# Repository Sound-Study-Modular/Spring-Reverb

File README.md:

# Spring-Reverb

The Spring Reverb is a flexible, easy-to-build voltage controlled DIY mono spring reverb module. Traditional guitar reverbs are tuned to the sound of the guitar and the amplifier it is played through. This circuit is different; designed to be relatively clean and high-fi, with a lot of bass response. It can also be abused and driven into (externally patched) feedback.

The circuit, plans and PCB/panel designs are open source and shared under Creative Commons.

- Works with a variety of spring reverb tanks, or with the Accutronics BTDR-2 reverb ‘brick’ designed by Brian Neunaber
- Includes PCB panel designs that can be very cheaply produced.
- Vactrol crossfade between dry and wet
- Tilt EQ on the reverb send to tune the voice of the reverb
- X-Fade input so the module can also be used as a standalone vactrol crossfader
- Attenuverter on the crossfade CV input
- Options for reverb tank connection and placement including front panel sockets.
- Optional (unbuffered) PCB connections for 100% wet and post-EQ dry outputs
- 6hp wide (NB: If using the brick, mounted horizontally, the brick extends 5mm over the PCB to the left of the module, around 25mm back from the front panel, so mount the reverb next to a shallow module)
- Around 60mm deep including a phono plug for the reverb tank coming from the back. Just 35mm deep if you mount the reverb connections on the front panel

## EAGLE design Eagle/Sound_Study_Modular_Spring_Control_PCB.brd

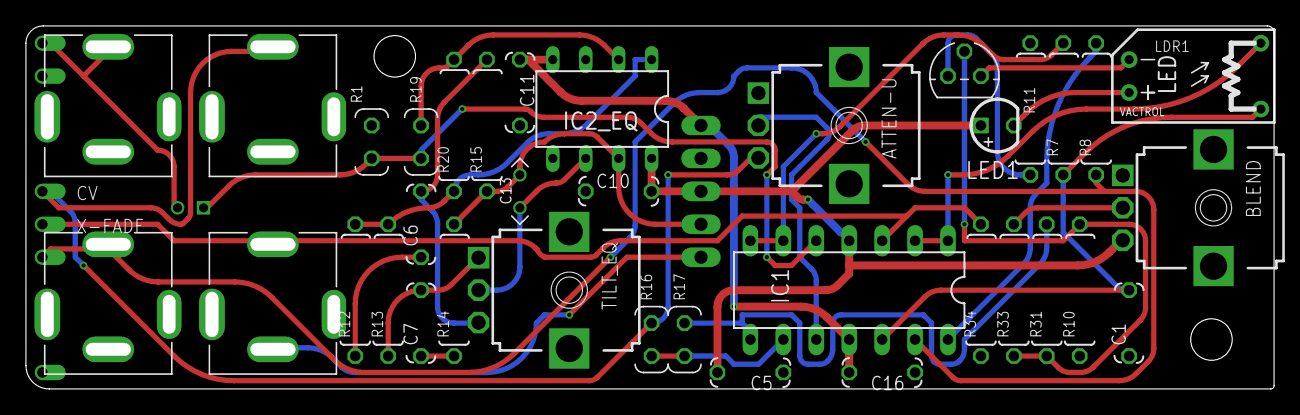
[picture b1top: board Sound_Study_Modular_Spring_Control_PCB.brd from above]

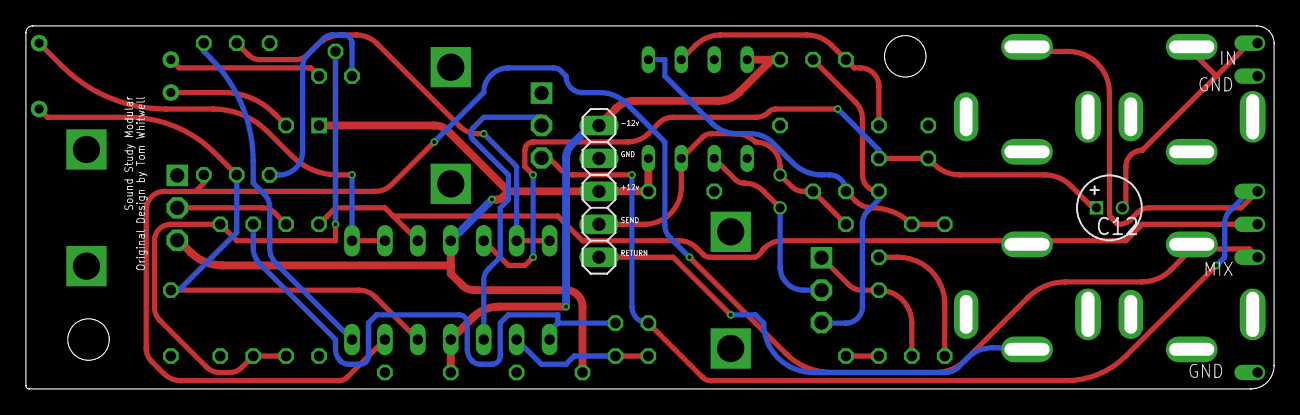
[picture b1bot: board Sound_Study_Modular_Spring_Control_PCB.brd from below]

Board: 4 copper layers, 96.3 x 28.0 mm, 44 parts (2 on the bottom side), 29 nets.

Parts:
ATTEN-U: 50k; EVUF
BLEND: 50k; EVUF
C1: 1nf; C050-024X044
C5, C10, C11, C16: 100n; C050-024X044
C6, C7: 33nf; C050-024X044
C12: 10uf; 050_020
C13: 22pf; 050X030_025
CV: ERTHENVAR
IC1: TL074; DIL14
IC2_EQ: NE5532; DIL08
IN: MONO_JACK_W_SWITCH; ERTHENVAR
JP3: 1X05
LDR1: VTL5C; VACTROL_COMPACT
LED1: 3mm Superbright; LED3MM
OUT: ERTHENVAR
R1: 100k; VERT-RESISTOR
R7: 0207/10
R8: 1k; 0207/10
R10, R31, R33, R34: 100k; 0207/10
R11, R12, R14: 2.2k; 0207/10
R13, R15: 6.8k; 0207/10
R16, R17: 47k; VERT-RESISTOR
R19: 10k; VERT-RESISTOR
R20: 10k; 0207/10
T1: 2N3904; TO92
TILT_EQ: 10k; EVUF
U$3: X-FADE; LONG_PAD_1
U$9, U$16: GND; LONG_PAD_1
U$13: IN; LONG_PAD_1
U$14: CV; LONG_PAD_1
U$17: MIX; LONG_PAD_1
X_FADE: ERTHENVAR

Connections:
+12V: BLEND.3, C5.2, C10.2, IC1.4, IC2_EQ.8, JP3.3, LED1.A
-12V: C11.1, C16.2, IC1.11, IC2_EQ.4, JP3.1
AUDIO_IN: C12.+, IC1.5, R1.1, R19.1
AUDIO_IN_BUF: IC1.6, IC1.7, R7.2
GND: ATTEN-U.1, BLEND.1, C1.1, C5.1, C10.1, C11.2, C16.1, CV.GND1, CV.GND2, IC2_EQ.3, IC2_EQ.5, IN.GND1, IN.GND2, JP3.2, OUT.GND1, OUT.GND2, R1.2, R10.1, R11.2, R34.1, U$9.P$1, U$16.P$1, X_FADE.GND1, X_FADE.GND2
MIX_OUT_B: IC1.13, OUT.TIP, R8.1, U$17.P$1
unnamed: C12.-, IN.TIP, U$13.P$1
unnamed: IC1.3, R34.2, U$3.P$1, X_FADE.TIP
unnamed: ATTEN-U.3, CV.TIP, R16.2, U$14.P$1
unnamed: C6.1, R12.1
unnamed: BLEND.2, R33.2
unnamed: IC1.14, R8.2
unnamed: C6.2, R15.2, TILT_EQ.3
unnamed: R11.1, T1.3
unnamed: C7.2, R13.1, TILT_EQ.1
unnamed: ATTEN-U.2, IC1.10
unnamed: C7.1, R14.1
unnamed: C13.1, IC2_EQ.6, TILT_EQ.2
unnamed: IC1.9, R16.1, R17.1
unnamed: IC2_EQ.2, R19.2, R20.2
unnamed: IC1.8, R17.2, R31.2
unnamed: LDR1.LED+, LED1.K
unnamed: IC2_EQ.1, R12.2, R13.2, R20.1
unnamed: R10.2, R31.1, R33.1, T1.2
unnamed: LDR1.LED-, T1.1
REVERB_RETURN_F: JP3.5, X_FADE.SWITCH
REVERB_SEND_F: C13.2, IC2_EQ.7, JP3.4, R14.2, R15.1
SUM: C1.2, IC1.12, LDR1.LDR_BOTTOM, R7.1
X_FADE_IN: IC1.1, IC1.2, LDR1.LDR_TOP
